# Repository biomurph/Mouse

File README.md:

# Mouse

### Repository for Open Source Mouse Firmware and Hardware
This repository holds the Arduino library, KiCAD PCB design files, gerber production files, BOM, and assembly instructions for the open-source computer mouse goodie bag item from the 2018 OSHWA Summit. The circuit design, PCB layout, and code were produced by Joel Murphy (aka biomurph | @SafeForRobots) in the Summer of 2018. The mouse wheel and wheel holder were designed in collaboration with Eugene Chang, and manufactured by [Tangible Creative](https://www.tangiblecreative.com). The production PCB boards were fabricated and stuffed by [Worthington Assembly](https://www.worthingtonassembly.com/). Thanks to Kelly Saxton for help in kitting and assembly instructions and the killer mouse morph gif! The microcontroller on board is a ATmega32u4 with Arduino Leonardo bootloader. This open-source mouse is a soldering kit, and comes pre-programmed with the example sketch from the Mousey Arduino library.

#### Assembly Instructions [Here](https://github.com/biomurph/Mouse/blob/master/AssemblyInstructions.md)
#### Library Functionality [Here](https://github.com/biomurph/Mouse/blob/master/LibraryFunctionality.md)
#### Hardware Design Files [Here](https://github.com/biomurph/Mouse/tree/master/Hardware)

## Anatomy of Mouse

### ADNS2620 !? That Went EOL Years Ago!
Yes, yes it did. Years ago, I tried to make a go of it in open-source hardware design, production and sales. I made something like [this](https://www.sparkfun.com/products/retired/10105) before SparkFun did, but it never got off the ground. I've been sitting on a small pile of components from those days, and this summer I decided that I have to chip away at that pile. So here you go. A fully functional computer mouse for you to hack and modify to your hearts delight. You're welcome!

If you are interested in modifying the design files to bring this project up to date, the one place that I have found that still sells these kinds of optical mouse sensors is a company called [PixArt](http://www.pixart.com.tw/index.asp) that has a variety of sensors to choose from. One of my goals is to do just that, so watch this repo if you want to be among the first to know when I have a working prototype.

### Installing The Firmware
Either download the ZIP of this repo or clone it. Then move or copy the file named `Mousey`
into your `Documents > Arduino > libraries` folder. Open or restart Arduino, Then
goto `File > Examples > Mousey > OpenMouse` to find the sketch that runs on OpenMouse.

# Use Your Mouse
This open-source computer mouse is built around an ATmega32u4 with the Arduino Leonardo bootloader. It has already been programmed with the example sketch from the Mousey library. There are two modes of operation HID and Not-HID. Modes are selected using the slide switch on the left side of the mouse.

## HID Mode
When the slide switch is on the side closest to the pad per hole prototyping area (aka DOWN), the mouse is in HID mode. When plugged into a micro USB cable, the mouse will read the sensors (wheel, buttons, optical sensor), and function just like a mouse attached to your computer!

## Not-HID Mode
When the slide switch is on the side closest to the 7 pin female header (aka UP), the mouse is in the Not-HID mode. When plugged into a micro USB cable, the mouse will read the sensors (wheel, buttons, optical sensor) and send the data it gets over serial at 115200 baud. You can open any serial terminal to view the data from the mouse.

## Troubleshooting
The mice were packaged with the HID select switch in the HID position. If you plug your mouse in to a computer and it doesn't work like a mouse should, then check to make sure that the HID switch is in HID mode. The small tact switch labeled `SW1` is the reset button for the Leonardo. You can switch modes on the fly, and press this reset button to change modes without unplugging your mouse. If all else fails, re-program the mouse with the OpenMouse.ino code from the example in the Mousey Library.

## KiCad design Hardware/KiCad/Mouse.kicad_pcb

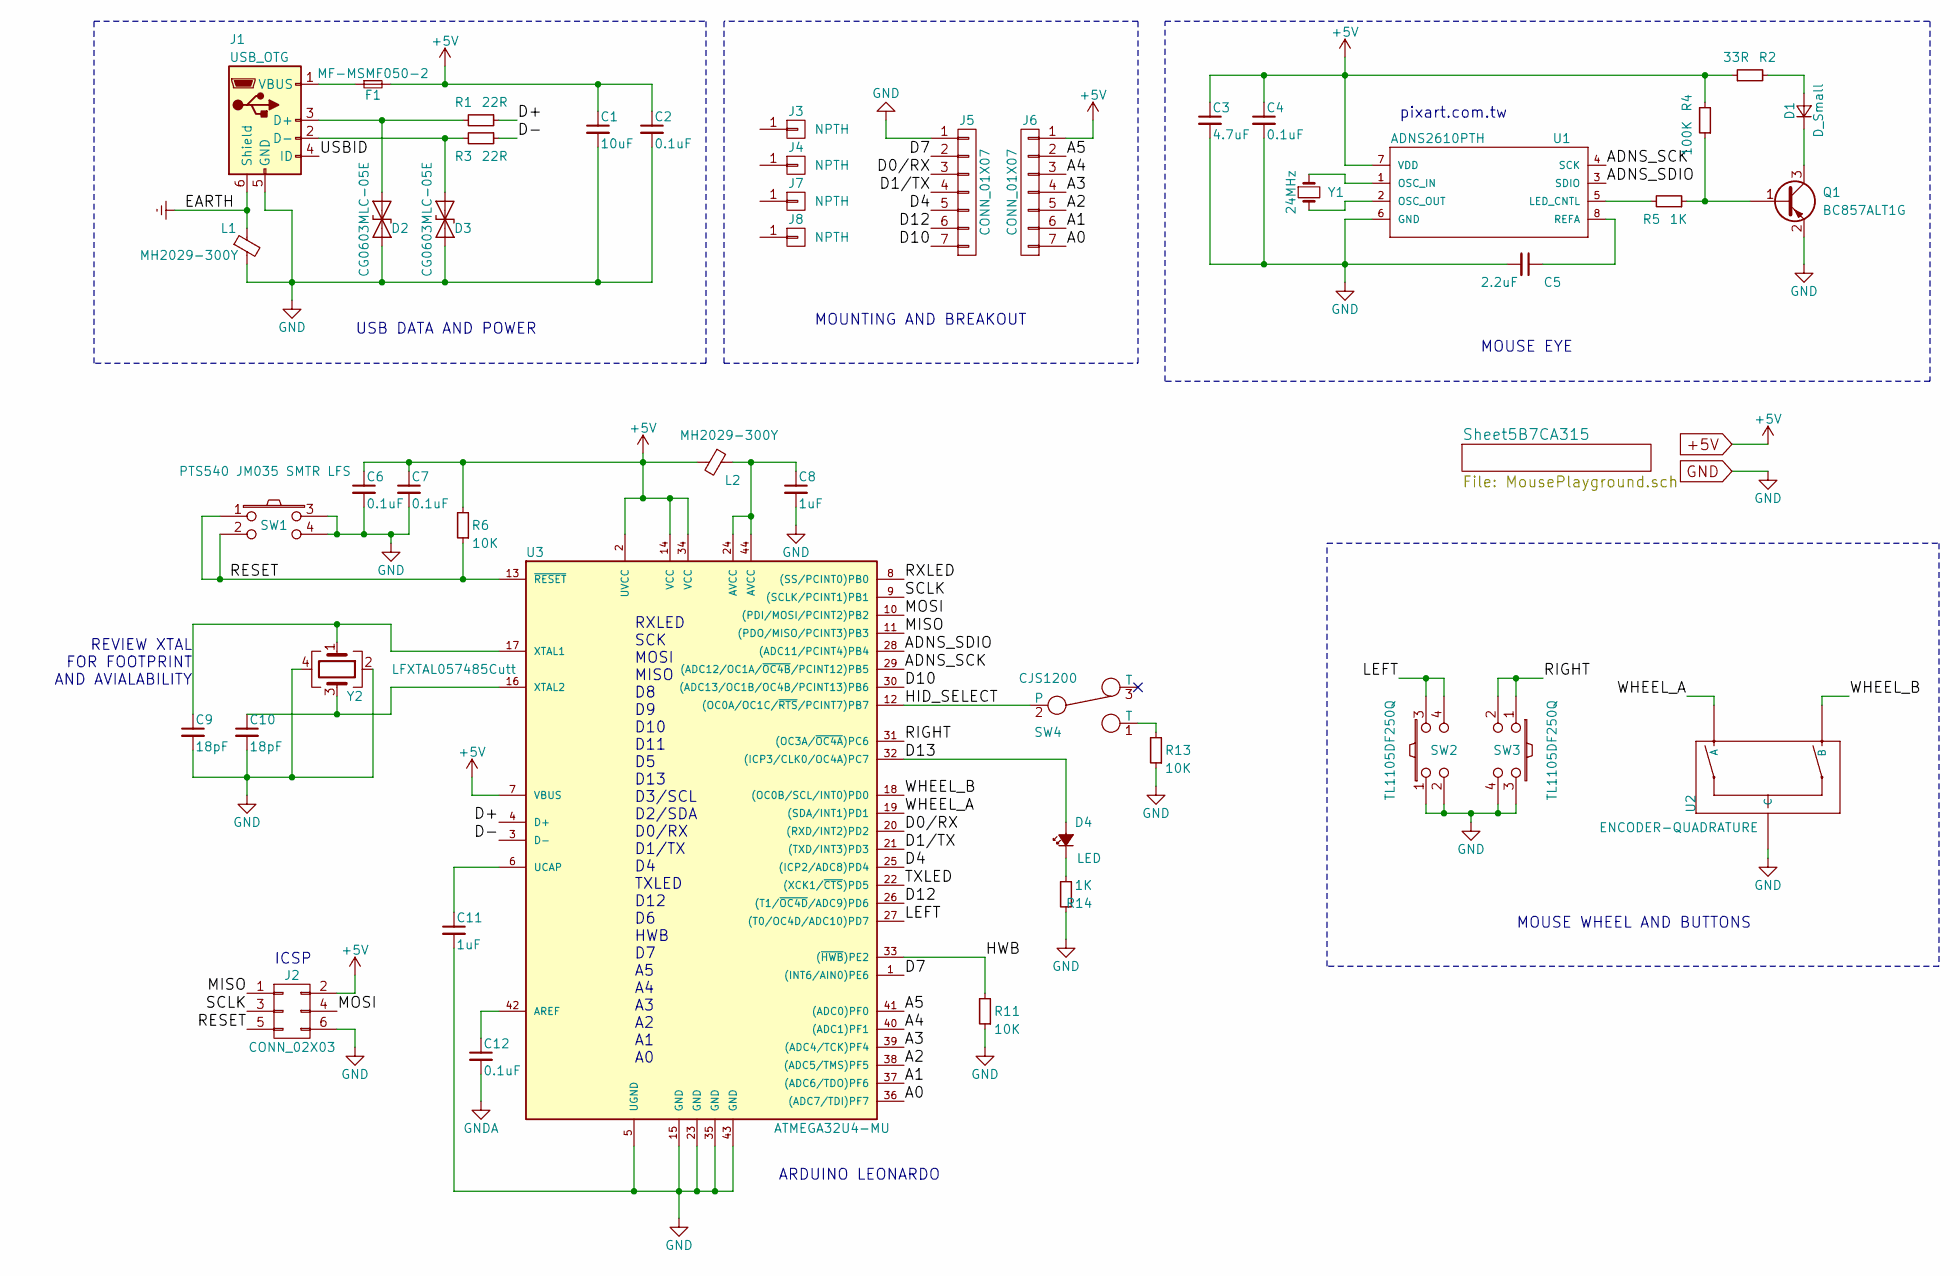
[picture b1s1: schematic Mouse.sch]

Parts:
C1: 10uF; C_0603
C2, C4, C6, C7, C12: 0.1uF; C_0603
C3: 4.7uF; C_0603
C5: 2.2uF; C_0603
C8, C11: 1uF; C_0603
C9, C10: 18pF; C_0603
D1: D_Small; LED_D5.0mm_Horizontal_O1.27mm_Z3.0mm
D2, D3: CG0603MLC-05E; C_0603
D4: LED; C_0603
F1: MF-MSMF050-2; C_1812
J1: USB_OTG; 10118193_microUSB
J2: CONN_02X03; Pin_Header_Straight_2x03_Pitch2.54mm_SMD
J3, J4, J7, J8: NPTH; NPTH_1875
J5, J6: CONN_01X07; Pin_Header_Straight_1x07_Pitch2.54mm
L1, L2: MH2029-300Y; C_0805
Q1: BC857ALT1G; SOT-23
R1, R3: 22R; C_0603
R2: 33R; C_0603
R4: 100K; C_0603
R5, R14: 1K; C_0603
R6, R11, R13: 10K; C_0603
SW1: PTS540 JM035 SMTR LFS; PTS540_Switch
SW2, SW3: TL1105DF250Q; Mouse_Button
SW4: CJS1200; SSSS810701_ALPS_DPDT
U1: ADNS2610PTH; ADNS2610
U2: ENCODER-QUADRATURE; Mouse_Encoder
U3: ATMEGA32U4-MU; LQFP-44_10x10mm_Pitch0.8mm
Y1: 24MHz; C_Disc_D5.0mm_W2.5mm_P5.00mm
Y2: LFXTAL057485Cutt; Crystal_SMD_3225-4pin_3.2x2.5mm

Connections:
+5V: C1.1, C2.1, C3.1, C4.1, C6.1, C7.1, F1.2, J2.2, J6.1, L2.2, R2.1, R4.2, R6.2, U1.7 (VDD), U3.2 (UVCC), U3.7 (VBUS), U3.14 (VCC), U3.34 (VCC); also elsewhere on the board
/A0: J6.7, U3.36 ((ADC7/TDI)PF7)
/A1: J6.6, U3.37 ((ADC6/TDO)PF6)
/A2: J6.5, U3.38 ((ADC5/TMS)PF5)
/A3: J6.4, U3.39 ((ADC4/TCK)PF4)
/A4: J6.3, U3.40 ((ADC1)PF1)
/A5: J6.2, U3.41 ((ADC0)PF0)
/ADNS_SCK: U1.4 (SCK), U3.29 ((ADC12/OC1A/~OC4B~/PCINT12)PB5)
/ADNS_SDIO: U1.3 (SDIO), U3.28 ((ADC11/PCINT4)PB4)
/D0/RX: J5.3, U3.20 ((RXD/INT2)PD2)
/D1/TX: J5.4, U3.21 ((TXD/INT3)PD3)
/D4: J5.5, U3.25 ((ICP2/ADC8)PD4)
/D7: J5.2, U3.1 ((INT6/AIN0)PE6)
/D10: J5.7, U3.30 ((ADC13/OC1B/OC4B/PCINT13)PB6)
/D12: J5.6, U3.26 ((T1/~OC4D~/ADC9)PD6)
/D13: D4.2 (A), U3.32 ((ICP3/CLK0/OC4A)PC7)
/D+: R1.1, U3.4 (D+)
/D-: R3.1, U3.3 (D-)
/HID_SELECT: SW4.2, U3.12 ((OC0A/OC1C/~RTS~/PCINT7)PB7)
/HWB: R11.2, U3.33 ((~HWB~)PE2)
/LEFT: SW2.3, SW2.4, U3.27 ((T0/OC4D/ADC10)PD7)
/MISO: J2.1, U3.11 ((PDO/MISO/PCINT3)PB3)
/MOSI: J2.4, U3.10 ((PDI/MOSI/PCINT2)PB2)
/RESET: J2.5, R6.1, SW1.1, SW1.2, U3.13 (~RESET~)
/RIGHT: SW3.1, SW3.2, U3.31 ((OC3A/~OC4A~)PC6)
/RXLED: U3.8 ((SS/PCINT0)PB0)
/SCLK: J2.3, U3.9 ((SCLK/PCINT1)PB1)
/TXLED: U3.22 ((XCK1/~CTS~)PD5)
/USBID: J1.4 (ID)
/WHEEL_A: U2.A, U3.19 ((SDA/INT1)PD1)
/WHEEL_B: U2.B, U3.18 ((OC0B/SCL/INT0)PD0)
Earth: J1.6 (Shield), J1.7, J1.8, J1.9, J1.10, J1.11, L1.1
GND: C1.2, C2.2, C3.2, C4.2, C5.2, C6.2, C7.2, C8.2, C9.2, C10.2, C11.2, D2.2 (A2), D3.2 (A2), J1.5 (GND), J2.6, J5.1, L1.2, Q1.2 (E), R11.1, R13.1, R14.2, SW1.3, SW1.4, SW2.1, SW2.2, SW3.3, SW3.4, U1.6 (GND), U2.4, U2.5, U2.C, U3.5 (UGND), U3.15 (GND), U3.23 (GND), U3.35 (GND), U3.43 (GND), Y2.2, Y2.4; also elsewhere on the board
GNDA: C12.2
unnamed: C5.1, U1.8 (REFA)
unnamed: C8.1, L2.1, U3.24 (AVCC), U3.44 (AVCC)
unnamed: C9.1, U3.17 (XTAL1), Y2.1
unnamed: C10.1, U3.16 (XTAL2), Y2.3
unnamed: C11.1, U3.6 (UCAP)
unnamed: C12.1, U3.42 (AREF)
unnamed: D1.1 (K), Q1.3 (C)
unnamed: D1.2 (A), R2.2
unnamed: D2.1 (A1), J1.3 (D+), R1.2
unnamed: D3.1 (A1), J1.2 (D-), R3.2
unnamed: D4.1 (K), R14.1
unnamed: F1.1, J1.1 (VBUS)
unnamed: Q1.1 (B), R4.1, R5.1
unnamed: R5.2, U1.5 (LED_CNTL)
unnamed: R13.2, SW4.1 (T)
unnamed: U1.1 (OSC_IN), Y1.1
unnamed: U1.2 (OSC_OUT), Y1.2

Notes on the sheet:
ICSP
pixart.com.tw
MOUSE WHEEL AND BUTTONS
MOUSE EYE
USB DATA AND POWER
ARDUINO LEONARDO
MOUNTING AND BREAKOUT
RXLED SCK MOSI MISO D8 D9 D10 D11 D5 D13 D3/SCL D2/SDA D0/RX D1/TX D4 TXLED D12 D6 HWB D7 A5 A4 A3 A2 A1 A0
REVIEW XTAL FOR FOOTPRINT AND AVIALABILITY

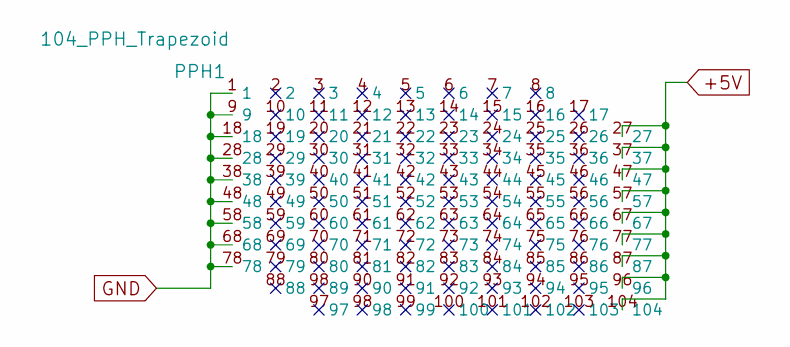
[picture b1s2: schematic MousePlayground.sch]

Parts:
PPH1: 104_PPH_Trapezoid; Mouse_PPH_Array

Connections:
+5V: PPH1.27, PPH1.37, PPH1.47, PPH1.57, PPH1.67, PPH1.77, PPH1.87, PPH1.96, PPH1.104; also elsewhere on the board
GND: PPH1.1, PPH1.9, PPH1.18, PPH1.28, PPH1.38, PPH1.48, PPH1.58, PPH1.68, PPH1.78; also elsewhere on the board

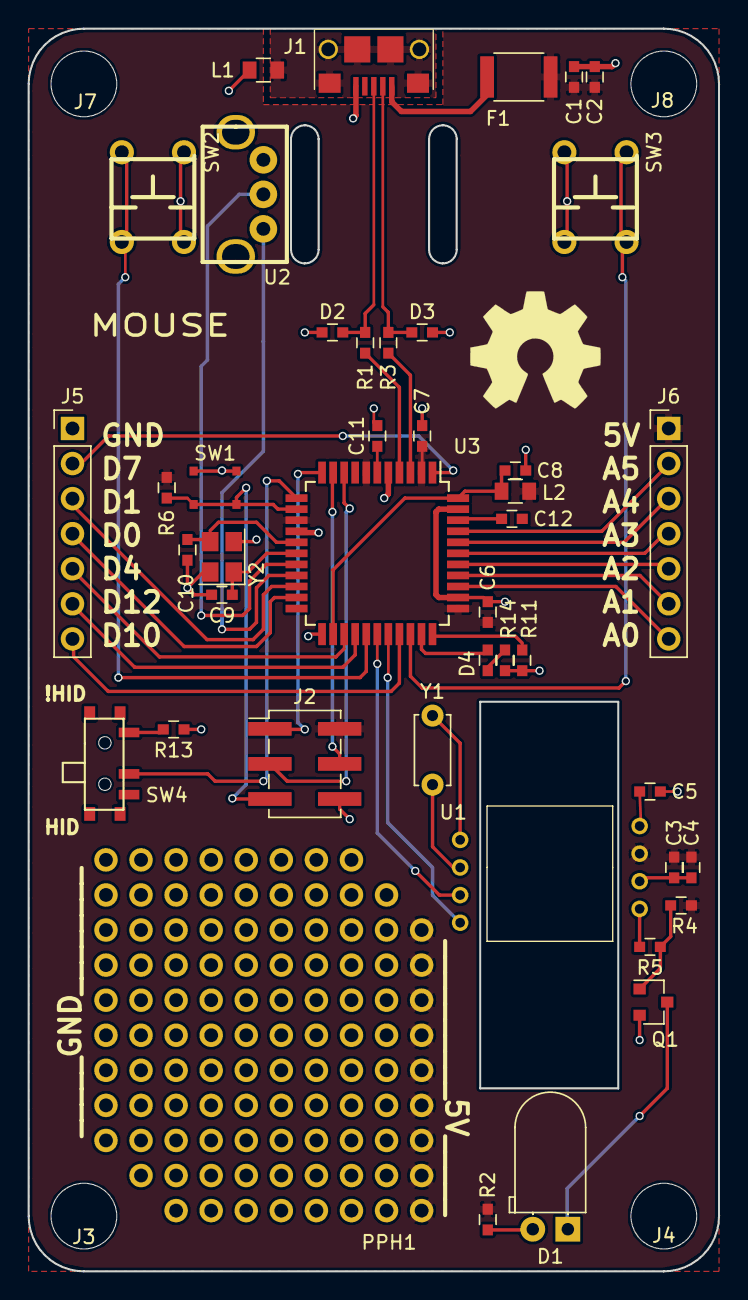
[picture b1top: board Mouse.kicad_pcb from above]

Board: 2 copper layers, 50.0 x 90.0 mm, 47 parts (0 on the bottom side), 47 nets.

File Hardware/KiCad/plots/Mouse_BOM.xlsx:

| MOUSE BOM
Id | Designator | Package | Quantity | Designation | Manufacturer | Part Number | Notes
1 | C1 | C_0603 | 1 | 10uF | Murata | GRM188R60J106KE47D
2 | C2,C4,C6,C7,C12 | C_0603 | 5 | 0.1uF | Yaego | CC0603ZRY5V7BB104
3 | C3 | C_0603 | 1 | 4.7uF | Taiyo | JMK107C6475MA-T
4 | C5 | C_0603 | 1 | 2.2uF | Yaego | CC0603ZRY5V6BB225
5 | C8,C11 | C_0603 | 2 | 1uF | Kemet | C0603C105Z9VACTU
6 | C9,C10 | C_0603 | 2 | 18pF | Kemet | C0603C180K5HACAUTO
7 | D1 | LED_D5.0mm_Horizontal_O1.27mm_Z3.0mm | 1 | DNP | DNP | DNP | DNP
8 | D2,D3 | C_0603 | 2 | TVS Varistor | Bourns | CG0603MLA-5.5ME
9 | D4 | C_0603 | 1 | LED | Wurth | 150060BS75000
10 | F1 | C_1812 | 1 | Fuse | Bel Fuse | 0ZCG0075FF2C
11 | J1 | 10118193_microUSB | 1 | USB_OTG | Amphenol | 10118193-0001LF
12 | J2 | Pin_Header_Straight_2x03_Pitch2.54mm_SMD | 1 | CONN_02X03 | DNP | DNP | DNP
13 | J5,J6 | Pin_Header_Straight_1x07_Pitch2.54mm | 2 | CONN_01X07 | Sullins | PPTC071LFBN-RC | DNP
14 | L1,L2 | C_0805 | 2 | Ferrite Bead | Bourns | MU2029-301Y
15 | Q1 | SOT-23 | 1 | PNP BEC | ON Semi | BC857ALT1G
16 | R1,R3 | C_0603 | 2 | 22R | Bourns | CR0603-JW-220ELF
17 | R2 | C_0603 | 1 | 33R | Panasonic | ERJ-3GEYJ330V
18 | R4 | C_0603 | 1 | 100K | Panasonic | ERJ-3GEYJ104V
19 | R5,R14 | C_0603 | 2 | 1K | Panasonic | ERJ-3GEYJ102V
20 | R6,R11,R13 | C_0603 | 3 | 10K | Stackpole | RNCP0603FTD10K0
21 | SW1 | PTS540_Switch | 1 | PTS540 JM035 SMTR LFS | C&K | PTS540JM035SMTRLFS
22 | SW2,SW3 | Push Button | 2 | SPST | E-Switch | TL1105DF250Q | DNP
23 | SW4 | SSSS810701_ALPS_DPDT | 1 | SPDT | Alps | SSSS810701
24 | U1 | ADNS2610 | 1 | ADNS2610PTH | DNP | DNP | DNP
25 | U2 | Mouse_Encoder | 1 | ENCODER-QUADRATURE | DNP | DNP | DNP
26 | U3 | LQFP-44_10x10mm_Pitch0.8mm | 1 | ATMEGA32U4-MU | Microchip | ATMEGA32U4RC-AU
27 | Y1 | C_Disc_D5.0mm_W2.5mm_P5.00mm | 1 | 24MHz Resonator | DNP | DNP | DNP
28 | Y2 | Crystal_SMD_3225-4pin_3.2x2.5mm | 1 | 16 MHz Crystal | Epson | FA-238 16.0000MB-C3

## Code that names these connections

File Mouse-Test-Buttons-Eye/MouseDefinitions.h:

#define ADNS_SCK  9
#define ADNS_SDIO 8
#define HID_SELECT  11
#define WHEEL_A 2
#define WHEEL_B 3
#define RIGHT 5
#define LEFT  6
#define LED 13

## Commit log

2018-08-06 First Test Code
2018-08-08 Got the eye and buttons working
2018-08-08 First stab at wheel support STL
2018-08-09 Added MouseEye. Compiles
2018-08-19 Cleaned up code and added mouse anatomy pic
2018-08-21 Added alternate mouse wheel support
2018-08-22 added the new Mousey library and fixed bugs.
2018-08-26 added design files
2018-08-31 corrected the .pos file
2018-09-20 updating the Mousey library
2018-09-20 relocated the Mousey library to it's own repo
2018-09-21 fixed a bug that made the scroll continue erroneously
2018-09-21 Moved working firmware into repo
2018-09-21 Really moved firmware in there this time
2018-09-22 formatting edits
2018-09-22 changed inputs to input pullup for production
2018-09-22 fixed serial formatting
2018-09-22 extended delay for better UX
2018-09-24 Added Lbrary function description and page for instructions
2018-09-25 Added pic of production Mouse
2018-09-26 Added assembly instructions and updated readme
2018-09-26 Removed unused images and resized images
2018-09-26 fixed broken links
2018-09-26 added board refs to instructions
2018-09-27 Add cropped photos for instructions to build mouse.
    edit 1
2018-09-27 added pics to assembly instructions
2018-09-27 added production pic to instructions
2018-09-27 formatting
2018-09-27 fixed pic name
2018-09-27 formatting and typos
2018-10-01 typos, edits, added STL for wheel parts
2018-10-03 Added caution about inserting the wheel holder
2018-10-07 minor edits
2018-10-19 Fixed varialble instance bug
2018-10-24 Repaired parts library paths
2020-02-14 ensuring this still works with KiCad
2020-05-01 Updated with correct ADNS number
2020-05-01 More typos.
2020-07-30 Added BOM !
2020-08-03 update with link to hardware files
2020-08-03 fixed bug in md
2021-04-23 Added support for older hardware and firmware
